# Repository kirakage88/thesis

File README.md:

# 🔧 Predictive Maintenance for Coiled Evaporators

> **Bachelor's Thesis** · Mechanical Engineering · Xavier University

---

## 💡 The Idea

Monitor aircon evaporator health in real time. Sensor data flows from ESP32 nodes through ESP-NOW to a TFT touchscreen, then up to the cloud. Machine learning models predict maintenance needs before failure hits.

---

## ⚡ How It Works

```
  🌡️ Sensors          📡 ESP-NOW           🖥️ TFT + ☁️ Cloud
  ┌──────────┐       ┌──────────┐        ┌──────────────┐
  │ BME280   │──────►│  Sender  │───────►│   Receiver   │
  │ DS18B20  │       │  ESP32   │  P2P   │  ESP32 + TFT │──► Supabase
  │ ×3 probes│       └──────────┘        └──────────────┘
  └──────────┘
```

**Ambient readings** (temp + humidity) + **3 probe temperatures** → calibrated → wireless → displayed + logged.

---

## 🗂️ Repo Map

```
thesis/
│
├── 📄 Thesis Proposal.pdf
│
├── 📂 codes/
│   ├── 📂 prototyping/                 # Final integrated builds
│   │   ├── ambient_module_final/       # Sensor fusion (BME280 + probes)
│   │   ├── now_ambient_sender/         # Wireless data transmitter
│   │   ├── now_receiver_supabase/      # Receiver + cloud pipeline
│   │   └── tft_complete/               # Display firmware (main UI)
│   │
│   ├── 📂 testing/                     # Component experiments
│   │   ├── BME280/  DS18B20/  probes/  i2c_scanner/
│   │   ├── now_sender/  now_receiver/  supabase/
│   │   ├── tft_display/  tft_touch/  tft_ui_demo/
│   │   └── ...                         # 15+ test sketches
│   │
│   └── 📂 python/machine learning/     # Classification experiments
│       ├── 0 perceptron.py
│       ├── 1 logistic_regression.py
│       ├── 2 SVM.py
│       ├── 3 dec_tree.py
│       ├── 4 random_forest.py
│       ├── 5 knn_classifier.py
│       └── pre-processing/
│
├── 📂 schematics/                      # Fritzing — circuits & PCBs
├── 📂 designs/                         # UI mockups, palette, fonts
└── 📂 resources/
```

---

## 🔌 Hardware

| Part | Interface | What It Does |
|------|-----------|--------------|
| ESP32-C3 Super Mini | — | Brains of the operation |
| BME280 | I2C (`0x76`) | Ambient temp + humidity |
| DS18B20 ×3 | OneWire (GPIO10) | Submerged probe temps |
| ST7789 240×320 TFT | SPI | Color display |
| XPT2046 | SPI (shared CLK) | Touch input |

### Calibration

```
BME280 Temp      →  raw × 1.0294412
BME280 Humidity  →  raw × 1.0579399
Probe A          →  1.701471 + 0.984997 × raw
Probe B / C      →  1.637417 + 0.9783362 × raw
```

---

## 🧠 Machine Learning

Six classifiers trained on sensor data — from classic Perceptron to Random Forest:

| # | Script | Model |
|---|--------|-------|
| 0 | `0 perceptron.py` | Perceptron |
| 1 | `1 logistic_regression.py` | Logistic Regression |
| 2 | `2 SVM.py` | Support Vector Machine |
| 3 | `3 dec_tree.py` | Decision Tree |
| 4 | `4 random_forest.py` | Random Forest |
| 5 | `5 knn_classifier.py` | K-Nearest Neighbors |

### Spin Up the Python Env

```bash
cd codes/python/machine learning

python -m venv .venv
# PowerShell:  .venv\Scripts\Activate.ps1
# Git Bash:    source .venv/Scripts/activate

pip install numpy matplotlib scikit-learn pandas

# Need deep learning later? Add PyTorch with CUDA:
pip install torch --index-url https://download.pytorch.org/whl/cu130
```

---

## 📐 Design

The TFT UI follows a **mobile-app navigation pattern** — persistent bottom bar, center arrow for a full-screen menu. Iron Grey palette with light/dark mode. Lora + Montserrat typography.

**Pages:** Main Menu → Pairing → Devices → Units → System

> Full mockups, palette shades, and component specs in `designs/tft_display/design_readme.md`.

---

## 🚀 Quick Start

**Firmware (Arduino)**
```bash
# 1. Arduino IDE + ESP32 board support
# 2. Install: TFT_eSPI, OneWire, DallasTemperature, Adafruit_BME280, esp_now, ESPSupabase
# 3. Open codes/prototyping/now_ambient_sender/
# 4. Board → ESP32-C3 Super Mini → Flash
```

**ML (Python)**
```bash
cd codes/python/machine learning
python -m venv .venv && source .venv/Scripts/activate
pip install numpy matplotlib scikit-learn pandas
python 0 perceptron.py
```

---

---

## 🛠️ Installation

**Git**
- Linux (Debian/Ubuntu): `sudo apt install git`
- macOS: `brew install git` or download from [git-scm.com](https://git-scm.com)
- ChromeOS: enable Linux (Crostini), then `sudo apt install git`
- Windows: download from [git-scm.com](https://git-scm.com)
- Verify: `git --version`

---

## ⚙️ Git Configuration

```bash
git config --global user.name "Your Name"
git config --global user.email "your_email@example.com"
git config --global init.defaultBranch main
```

- If using GitHub's privacy feature, use the provided private email: `username@users.noreply.github.com`
- Verify: `git config --global user.name` and `git config --global user.email`
- **macOS:** ignore `.DS_Store` files globally to prevent metadata files from appearing in commits:

```bash
echo ".DS_Store" >> ~/.gitignore_global
git config --global core.excludesFile ~/.gitignore_global
```

---

## 🌐 GitHub Account Setup

- Use a **real email** — required for contribution tracking
- Enable privacy settings: keep email private, block CLI pushes that expose personal email
- Enable **2FA** using a TOTP app (Google Authenticator, Authy, etc.)
  - ⚠️ **Warning:** losing 2FA credentials **and** recovery codes means permanent account lockout — GitHub Support cannot restore access

---

## 🔑 SSH Key Authentication

Check for an existing key:

```bash
ls ~/.ssh/id_ed25519.pub
```

Generate a new Ed25519 key:

```bash
ssh-keygen -t ed25519 -C "your_email@example.com"
```

- Press Enter to accept the default location
- Optional: set a passphrase for extra security

Copy the public key:

```bash
cat ~/.ssh/id_ed25519.pub
```

It starts with `ssh-ed25519` and ends with `username@hostname`.

**Add to GitHub:**
1. Settings → SSH and GPG keys → New SSH Key
2. Paste the public key as an **Authentication Key**

Test the connection:

```bash
ssh -T git@github.com
```

- Success: `"Hi username! You've successfully authenticated, but GitHub does not provide shell access."`
- Failure: retry or ask for help in TOP Discord

Multiple SSH keys can be linked to one GitHub account — one per machine.

---

*Built with ☕ and late nights by **Kira (JRon)** · JPSME-XUC · Xavier University*

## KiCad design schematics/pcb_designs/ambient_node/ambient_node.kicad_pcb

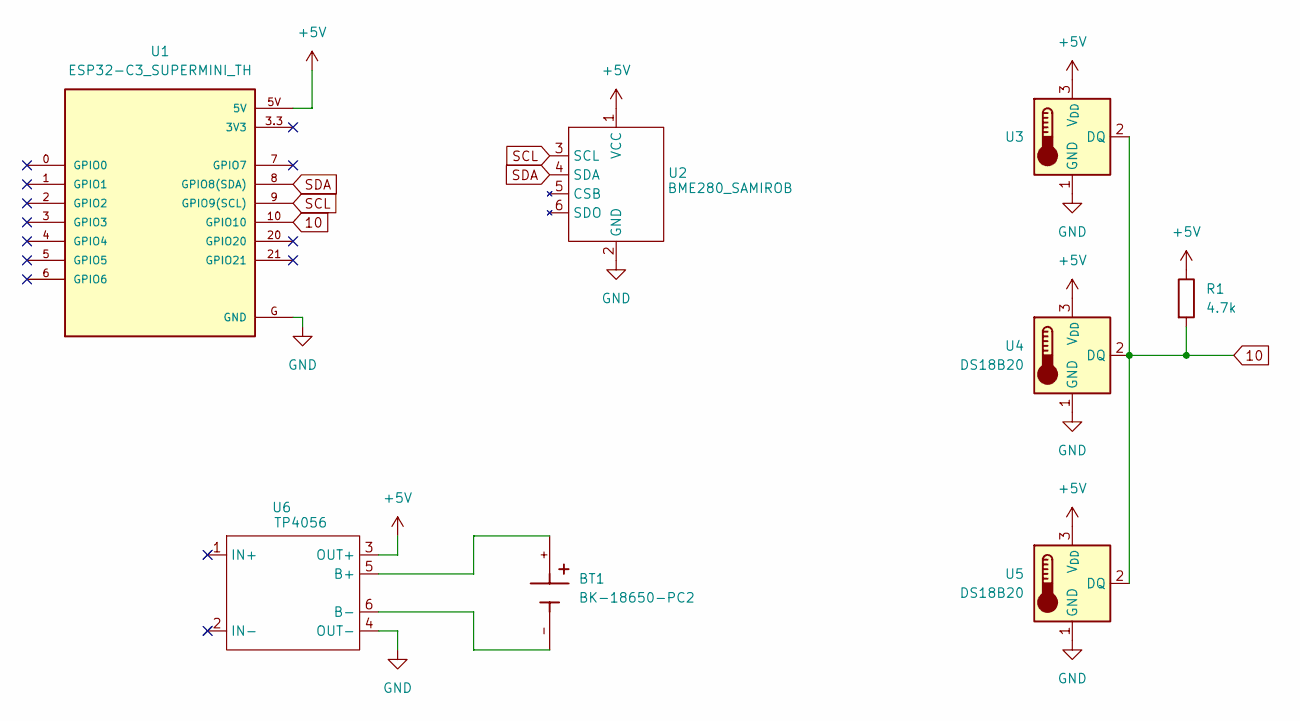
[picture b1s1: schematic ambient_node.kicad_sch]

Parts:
BT1: BK-18650-PC2; BAT_BK-18650-PC2; PARTREV F
R1: 4.7k; R_Axial_DIN0204_L3.6mm_D1.6mm_P5.08mm_Horizontal
U1: ESP32-C3_SUPERMINI_TH; MODULE_ESP32-C3_SUPERMINI_TH
U2: BME280_SAMIROB
U3, U4, U5: DS18B20; TO-92_Inline
U6: TP4056; TP4056-Module

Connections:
10: R1.2, U1.10 (GPIO10), U3.2 (DQ), U4.2 (DQ), U5.2 (DQ)
+5V: R1.1, U1.5V, U2.1 (VCC), U3.3 (V_{DD}), U4.3 (V_{DD}), U5.3 (V_{DD}), U6.3 (OUT+)
GND: U1.G (GND), U2.2 (GND), U3.1 (GND), U4.1 (GND), U5.1 (GND), U6.4 (OUT-)
unnamed: BT1.+, U6.5 (B+)
unnamed: BT1.-, U6.6 (B-)
SCL: U1.9 (GPIO9(SCL)), U2.3 (SCL)
SDA: U1.8 (GPIO8(SDA)), U2.4 (SDA)

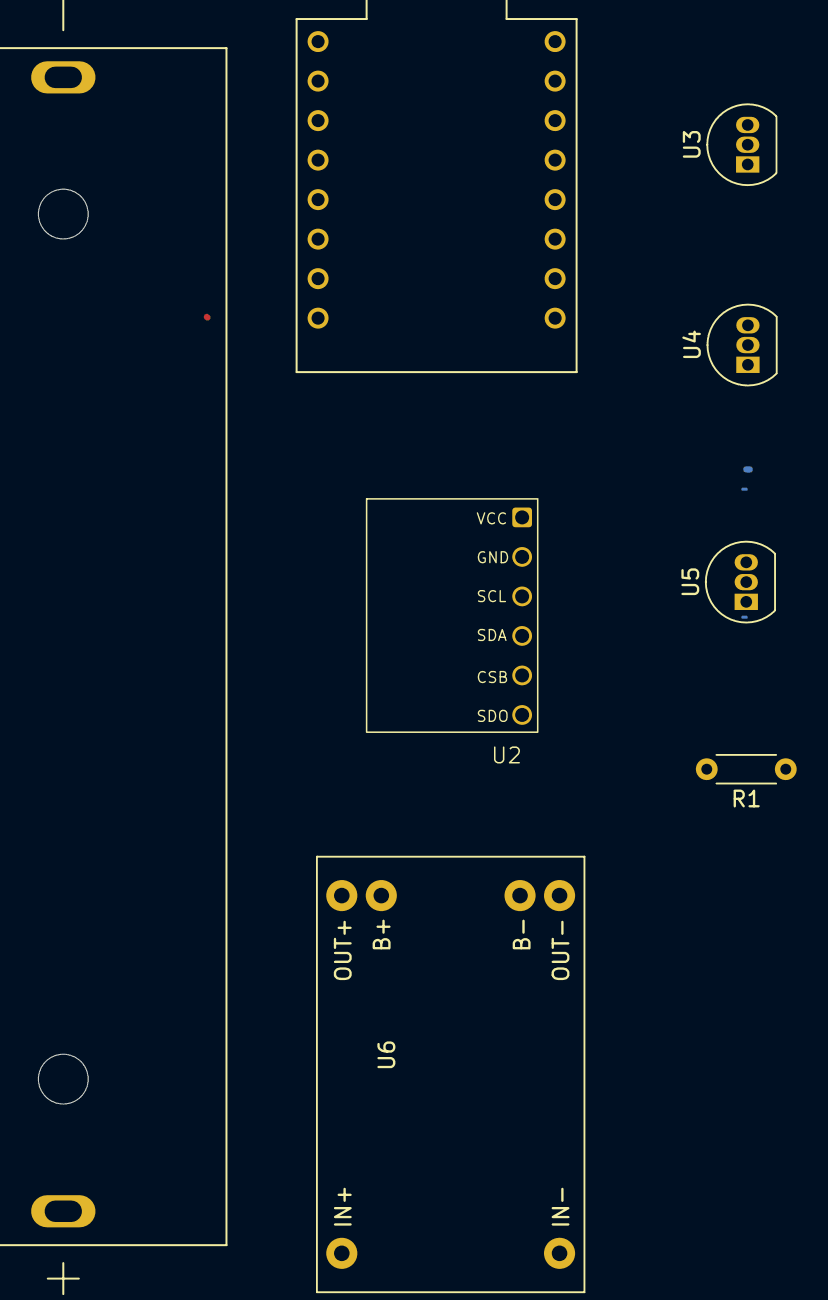
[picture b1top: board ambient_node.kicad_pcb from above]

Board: 4 copper layers, 8 parts (0 on the bottom side), 7 nets.

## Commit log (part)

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2026-06-21 Update header from 'thesis' to 'Thesis'
2026-06-21 Added Designs Folder for TFT Display
2026-06-21 Added Schematics and Thesis Proposal Document
2026-06-21 Added Codes Folder and a dedicated README.md
2026-06-21 Added codes for Machine Learning
2026-06-21 Added Codes for Deep Learning and Requirements.txt for Virtual Environments
2026-06-21 Fixed codes_readme.md and Added README.md
2026-06-21 Added README.md and updated codes_readme.md
2026-06-21 Added resources
2026-06-23 Added TFT Navbar Variations
2026-06-23 Added new Logo
2026-06-23 Added Navigation Bar, Icons with Active and Inactive States, updated Design and Code
2026-06-30 Added gitignore for Agents.md
2026-06-30 Add MPU6050 test sketch & libraries
    - testing/mpu6050/: MPU6050 test sketch with Adafruit_MPU6050 library
    - Patched Adafruit_MPU6050 WHO_AM_I check to accept 0x70 (MPU6500/clone)
    - Added Adafruit_SSD1306 OLED library
    - Added MPU6050.fzz schematic
    - Added AGENTS.md with repo guidance
    - Removed root .gitignore (previously only ignored AGENTS.md)
